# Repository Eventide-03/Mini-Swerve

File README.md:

# Swerve Drivetrain

A fully custom four-module swerve drivetrain built to replicate the FRC/FTC swerve drivetrains. Every part of this project was designed/planned by me.

## Project Resources

- **[CAD (Onshape)](https://cad.onshape.com/documents/22f3425ea7c3c5baea4db72a/w/41cf12666249611bfbd4a57b/e/570cbec20c3995e10be4fe6f?renderMode=0&uiState=6a05716b29587ab90c126fd3)** — full mechanical assembly and exploded views
- **[Bill of Materials (Google Sheets)](https://docs.google.com/spreadsheets/d/13JzB3kvO0vG1ZuJ61luXd1x6dMnEUsCQSgEZeQXHTig/edit?usp=sharing)** — every part, quantity, and source
- **[Calculations (Google Docs)](https://docs.google.com/document/d/1093Fhib_KALhrss7tIt823cWR-YH7OZk02LRxrgmfjs/edit?usp=sharing)** — gear ratios, motor sizing, and drivetrain math

## Overview

Swerve drive is an omnidirectional drivetrain, which means each wheel module can independently steer and drive, allowing a robot to move and rotate at the same time. I thought it would be nice to make a tinier at-home version for my own enjoyment, normally they are pretty big, but this one is fun sized.

This build has the full swerve control system on a 12.25 × 12.25 inch chassis with four independent modules. Each module uses 5010 brushless motors for driving and steering, using gear reductions to achieve the required torque. This leaves us with a miniature platform that actslike a full-size competition swerve, but small enough to use in my own house.

In order to save money I designed a custom PCB in order to hold everything, making it much easier to wire. In addition I will be using my SpeedyBee f405 to control the drive motors to avoid having to pay for 4 extra motor controllers.

## Specifications

| Attribute | Detail |
|---|---|
| Chassis footprint | 12.25 × 12.25 in |
| Modules | 4 (independent steer + drive) |
| Motors | 8 × 5010 360 kV brushless (4 drive, 4 steer) |
| Reduction | 8:1 per axis |
| Master controller | ESP32-S3-DevKitC-1 |
| Steering control | 2 × Makerbase (MKS) ESP32 Dual FOC ESC, controlled over UART via SimpleFOC Commander |
| Drive control | SpeedyBee F405 4-in-1 ESC (DSHOT600) |
| Steering feedback | 4 × AS5600 magnetic encoders (I²C) |
| Radio control | RadioMaster Pocket ELRS (TX + receiver) |
| Power | 4S LiPo (14.8 V) → Mini-360 buck converter (5 V) for logic |

## Architecture

The ESP32-S3-DevKitC-1 runs most of the code and is the brain reading commands from the ELRS receiver, and running the swerve kinematics, and sending the commands to the two motor-control subsystems:

- **Driving:** The master sends DSHOT600 signals to the SpeedyBee F405 4-in-1 ESC, which drives the four drive motors.
- **Steering:** The master sends addressed commands over a shared UART bus to two MKS ESP32 Dual FOC boards (using [SimpleFOC](https://simplefoc.com/) Commander). Each board runs field-oriented control on two steering motors, using an AS5600 magnetic encoder per module for absolute angle feedback.

All of this lives on the carrier PCB that seats the ESP32-S3 and breaks out clean, labeled connectors for the ESC, MKS boards, encoders, receiver, and power.

> **Important:** The steering magnets must be diametrically magnetized (poles across the diameter, not top-to-bottom), 6 × 2.5 mm, and mounted on the steering rotation axis, not the motor shaft or drive shaft. The AS5600 reports an absolute 0–360°, so it must rotate 1:1 with the module's steering angle.

---

## Assembly Instructions

Work through these in order. Use the **[CAD exploded views](https://cad.onshape.com/documents/22f3425ea7c3c5baea4db72a/w/41cf12666249611bfbd4a57b/e/570cbec20c3995e10be4fe6f?renderMode=0&uiState=6a05716b29587ab90c126fd3)** go to the assembly and click the exploded views to the left.

### 1. Gather parts
Order everything on the **[BOM](https://docs.google.com/spreadsheets/d/13JzB3kvO0vG1ZuJ61luXd1x6dMnEUsCQSgEZeQXHTig/edit?usp=sharing)** and 3D-print the printed components from the CAD. Confirm you have all fasteners, belts, bearings, and magnets before starting.

### 2. Populate and solder the PCB
- Solder the through-hole headers and connectors to the custom carrier board, following the silkscreen labels.
- Solder the decoupling capacitors near the ESP32 5 V pin.
- Solder the pin-socket rows that the ESP32-S3-DevKitC-1 plugs into.
- **Before powering anything, use a multimeter to verify there are no shorts** between 5 V, GND, and the battery rails.

### 3. Wire the drive ESC (SpeedyBee F405)
- Connect the four drive-motor signal lines and a shared ground from the SpeedyBee ESC to the DSHOT header on the carrier board.
- Use only the M1–M4 signal pads plus one GND pad (verify GND with a multimeter first — M5–M8 pads on the board have no hardware behind them).

### 4. Wire the steering controllers (MKS ESP32 Dual FOC)
- Connect each MKS board's UART (TX/RX/GND) to the shared steering UART nets on the carrier board.
- Both boards share the bus and are addressed individually in firmware via SimpleFOC Commander.

### 5. Set up the encoders (AS5600)
- Mount each AS5600 so its chip faces the diametrically-magnetized magnet on the **steering rotation axis** of each module.
- Wire each encoder's VCC / GND / SDA / SCL to its MKS board's encoder header, and tie DIR to GND.
- Before final assembly, flash SimpleFOC firmware to the MKS boards, configure the motors, and run encoder calibration for each module.

### 6. Assemble the mechanical drivetrain
- Build the four swerve modules and mount them to the chassis per the **[CAD exploded views](https://cad.onshape.com/documents/22f3425ea7c3c5baea4db72a/w/41cf12666249611bfbd4a57b/e/570cbec20c3995e10be4fe6f?renderMode=0&uiState=6a05716b29587ab90c126fd3)**.
- Install belts, bearings, and wheels; verify each module steers freely and each drive wheel spins without binding.

### 7. Power distribution
- Wire the 4S LiPo through the switch and fuse, then split to the SpeedyBee ESC, both MKS boards, and the Mini-360 buck converter input.
- The buck's 5 V output feeds the carrier board's logic rail (ESP32 + receiver). **The battery's 14.8 V never reaches the carrier board directly** — only the buck input does.

### 8. Flash the ESP32-S3 and bring it up
- Open the firmware in **[Arduino IDE 2.x](https://www.arduino.cc/en/software)** and select the **ESP32S3 Dev Module** board.
- Bring the system up progressively rather than all at once:
  1. **Smoke test** — confirm the board powers and blinks.
  2. **Drive test** — verify DSHOT control of a single drive motor.
  3. **Steering test** — send a UART target to an MKS board and confirm the steering motor holds position.
  4. **Receiver test** — confirm the ESP32 reads ELRS channels.
- Once each subsystem checks out, run the full firmware to read the transmitter, compute swerve kinematics, and drive all eight motors together.

---

## Notes

- Some ESP32-S3-DevKitC-1 revisions have different row spacing (22.86 mm vs 25.4 mm), measure your board with calipers before finalizing the PCB.
- Measure the Mini-360 buck module's pad spacing with calipers as well before ordering the board.
- The library APIs (DSHOT, SimpleFOC, ELRS) may need small adjustments to match current versions, adapt from each library's examples.

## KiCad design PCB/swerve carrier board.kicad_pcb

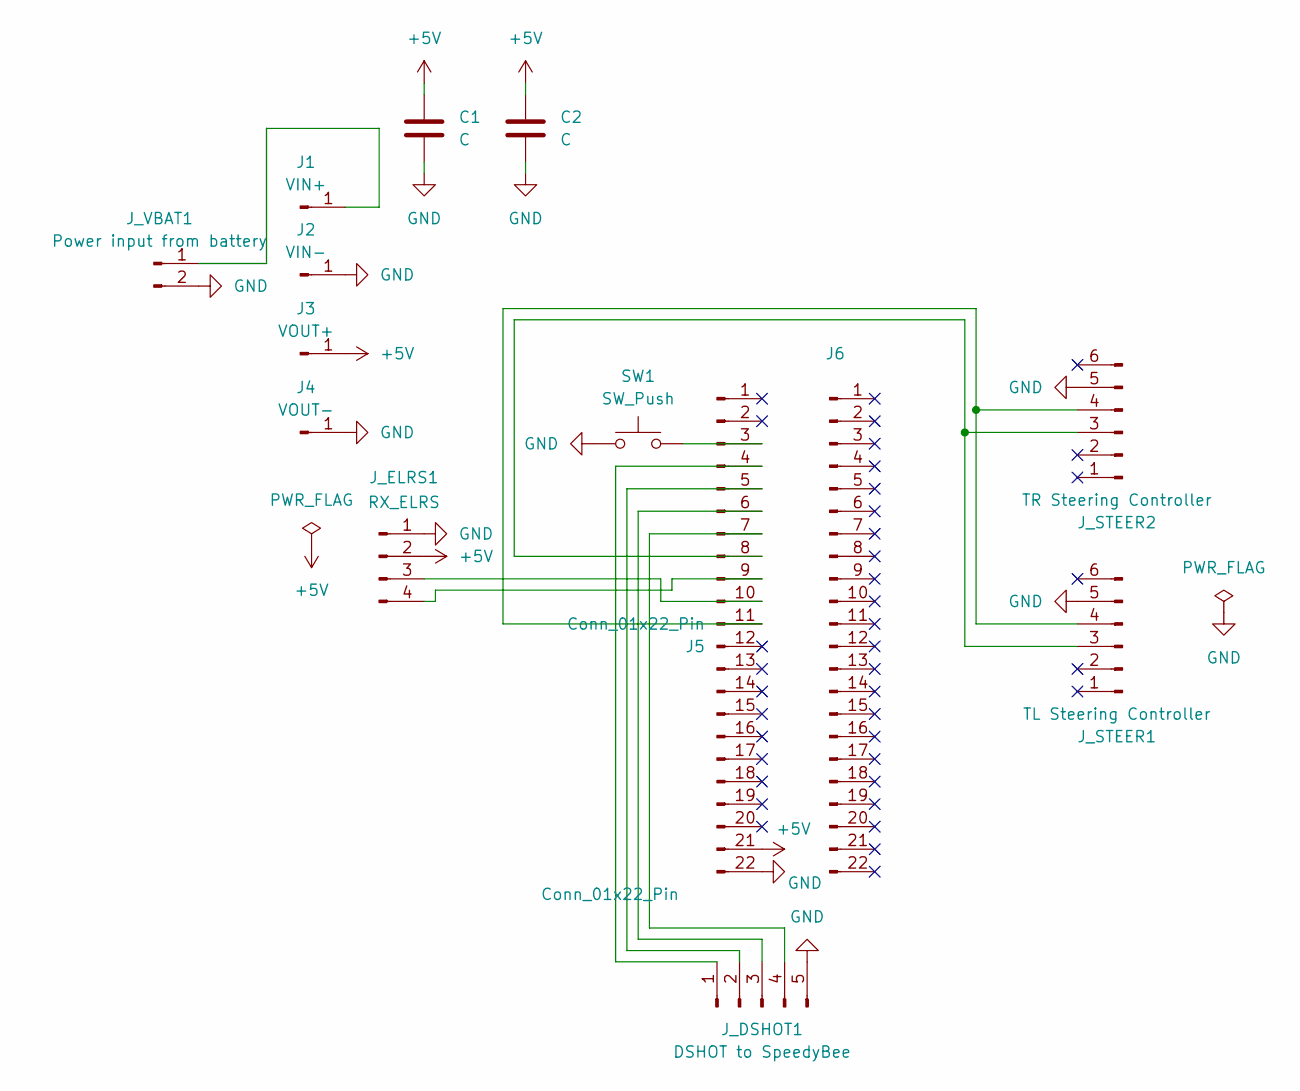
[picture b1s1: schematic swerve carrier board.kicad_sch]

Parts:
C1, C2: C; CP_Radial_D5.0mm_P2.50mm
J1: VIN+; PinHeader_1x01_P2.54mm_Vertical
J2: VIN-; PinHeader_1x01_P2.54mm_Vertical
J3: VOUT+; PinHeader_1x01_P2.54mm_Vertical
J4: VOUT-; PinHeader_1x01_P2.54mm_Vertical
J5: Conn_01x22_Pin; PinSocket_1x22_P2.54mm_Vertical_SMD_Pin1Left
J6: Conn_01x22_Pin; PinSocket_1x22_P2.54mm_Vertical_SMD_Pin1Right
J_DSHOT1: DSHOT to SpeedyBee; PinHeader_1x05_P2.54mm_Vertical
J_ELRS1: RX_ELRS; PinHeader_1x04_P2.54mm_Vertical
J_STEER1: TL Steering Controller; PinHeader_1x06_P2.54mm_Vertical
J_STEER2: TR Steering Controller; PinHeader_1x06_P2.54mm_Vertical
J_VBAT1: Power input from battery; PinHeader_1x02_P2.54mm_Vertical
SW1: SW_Push; SW_Cherry_MX_1.00u_PCB

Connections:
+5V: C1.1, C2.1, J3.1 (Pin_1_1), J5.21, J_ELRS1.2
GND: C1.2, C2.2, J2.1 (Pin_1_1), J4.1 (Pin_1_1), J5.22, J_DSHOT1.5, J_ELRS1.1, J_STEER1.5, J_STEER2.5, J_VBAT1.2, SW1.1
unnamed: J1.1 (Pin_1_1), J_VBAT1.1
unnamed: J5.3, SW1.2
unnamed: J5.4, J_DSHOT1.1
unnamed: J5.5, J_DSHOT1.2
unnamed: J5.6, J_DSHOT1.3
unnamed: J5.7, J_DSHOT1.4
unnamed: J5.8, J_STEER1.3, J_STEER2.3
unnamed: J5.9, J_ELRS1.4
unnamed: J5.10, J_ELRS1.3
unnamed: J5.11, J_STEER1.4, J_STEER2.4

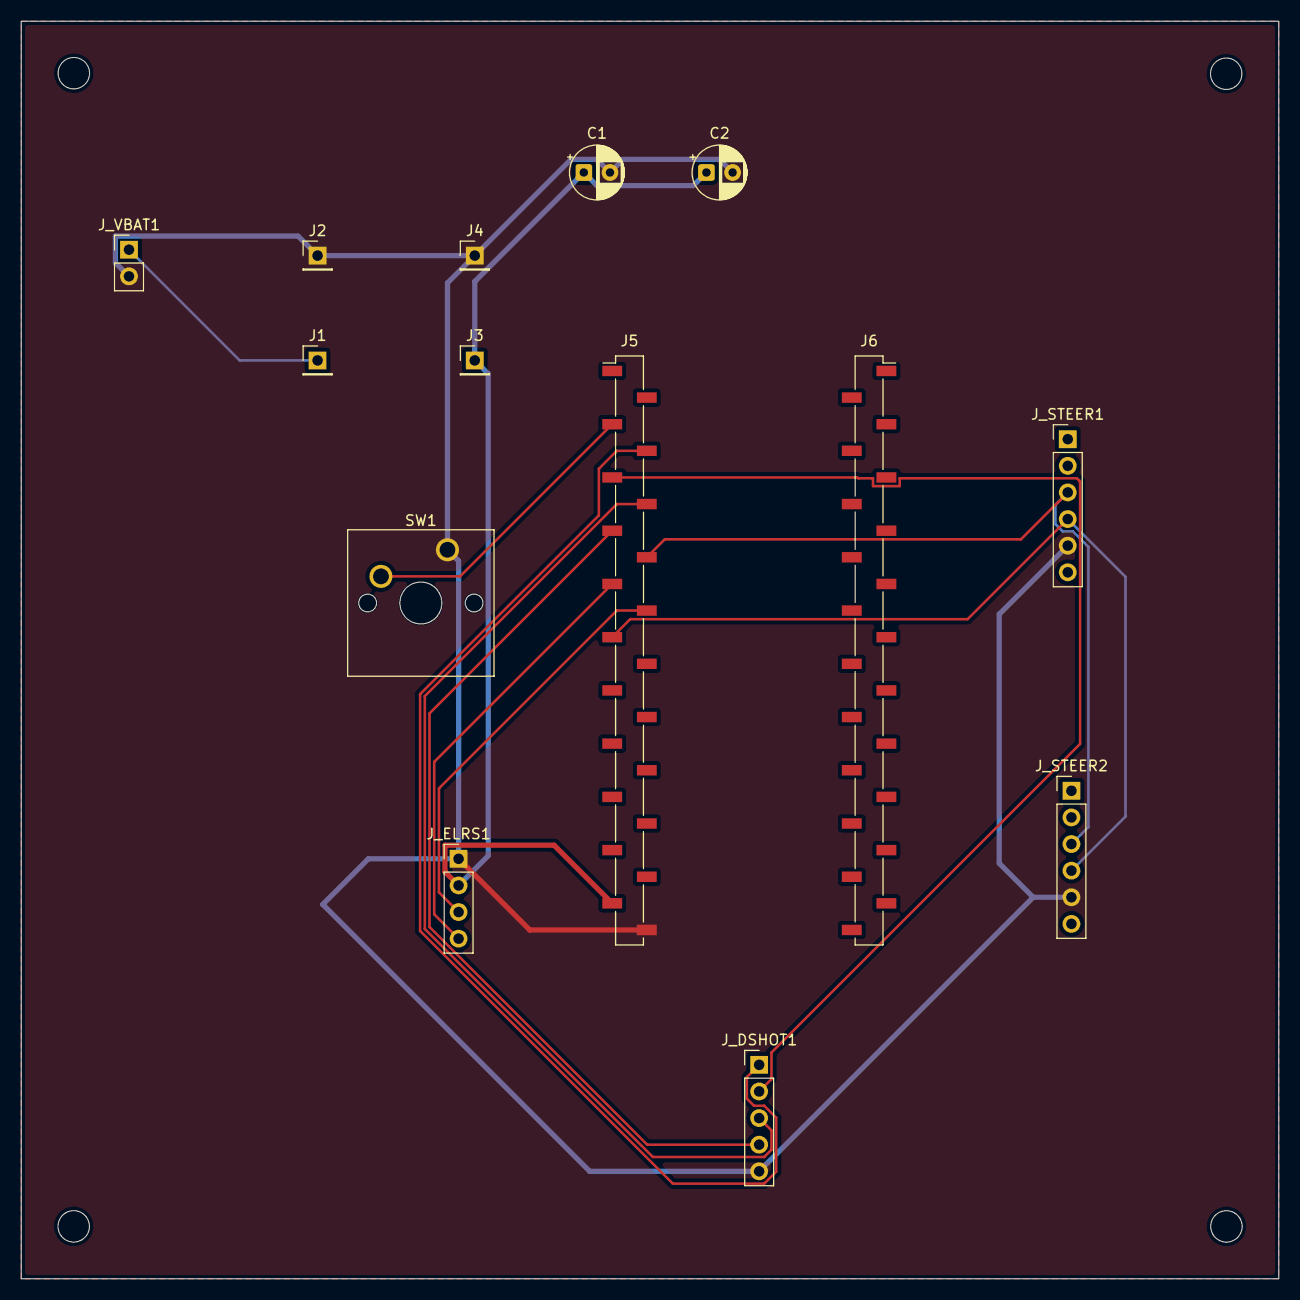
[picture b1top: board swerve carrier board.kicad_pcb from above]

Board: 2 copper layers, 120.0 x 120.0 mm, 14 parts (0 on the bottom side), 12 nets.

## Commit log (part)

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2026-05-14 Add CAD document link to README
    Added a link to the CAD document for the project.
2026-05-17 Update README with CAD and BOM links
    Added links to CAD and BOM resources.
2026-05-26 added pcb files
2026-05-26 Add link to calculations document in README
2026-05-26 fixed formatting
2026-05-26 added bom
2026-05-26 added code testing
2026-05-26 Enhance README with design details and images
    Added additional details about the mini swerve design, including dimensions, images, and links to CAD and BOM.
2026-05-26 fixed formatting of README
